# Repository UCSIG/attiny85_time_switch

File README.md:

# ATtiny85 Time Switch

## Low-power 12/24V time switch with undervoltage protection using the internal oscillator of the ATtiny85

The aim of this project is to switch a load on and off in regular time intervals. The device itself consumes only very little sleep current (~19.6uA on average).  
The device also monitors the supply voltage and turns off the load if the supply drops lower than the defined threshold.

## Features

- Clock calibration algorithm with values stored in the internal eeprom
- Supply voltage monitoring
- Jumper configuration for feature selection (supply voltage monitoring + time switch/only supply voltage monitoring)
- Jumper configuration for undervoltage threshold selection (12/24V)
- Low current consumption (~19.6uA)

## Specifications

| Type                        | Value        |
| --------------------------- | ------------ |
| Average Current Consumption | 19.6uA       |
| Maximum Load Current        | 5.7A (cont.) |
| Supply Voltages             | 12/24V       |
| Switch Type                 | Low-Side     |

## Detailed Description

There are three jumpers which must be set to either select the 12V or the 24V configuration. This changes the on/off times as well as the undervoltage thresholds.  
Every time the jumper configuration is changed, a reset must be performed for the changes to take effect.  

Upon coming out of reset, the device reads its clock calibration values stored in the internal eeprom to provide accurate timings for the time switch.

The device wakes up periodically and immediately goes back to sleep. That way, very long deep sleep periods can be reached.  
The ATtiny85 runs off of the internal 128kHz low speed oscillator during deep sleep. The watchdog timer wakes up the device every 8.192s (the maximum watchdog timeout) and the ATtiny increments a counter variable.
If it surpasses a pre-defined threshold, the load switch changes state from on->off or the other way round.  

Every 15 minutes it also measures the supply voltage and compares it to a pre-defined threshold. If the supply is lower than that threshold, the load is switched off until the device is reset.  
The maximum load current is determined by the sizing of the n-fet Q1. With the n-fet PMV20XNER one can switch up to 5/7A. The load is switched with a low side switch.  

The internal 8MHz oscillator of the ATtiny85 is used as the primary clock source. However, the clock frequency can vary by up to ±15%. In order to get accurate on/off times from the time switch,
this internal oscillator must be calibrated. A detailed description of how to do that can be found [here](clock_calibrations/clock_calibrations.md).

## Mechanical

The pcb is designed to fit in the [EL111](https://ide.es/eng/products/junction-boxes-and-mechanisms/ip65-ip67-junction-boxes/ref_EL111) enclosure by IDE electric.
It is screwed into the case using four M4 screws. The case itself is rated IP65-67. Its dimensions are 113x113x68 mm (Height x Width x Depth).

## Project structure

The code resides in the folder `src` and `include`. PlatformIO is chosen as the build environment. The best way to program the ATtiny85 is to use PlatformIO and VS Code as the IDE.  
The pcb project can be found under `pcb_project/attiny85_time_switch`. The relevant code snippets for changing the timing values and the undervoltage thresholds are at the top of `main.cpp`.
The gerber files are in `pcb_project/attiny85_time_switch/fabrication_outputs/`.

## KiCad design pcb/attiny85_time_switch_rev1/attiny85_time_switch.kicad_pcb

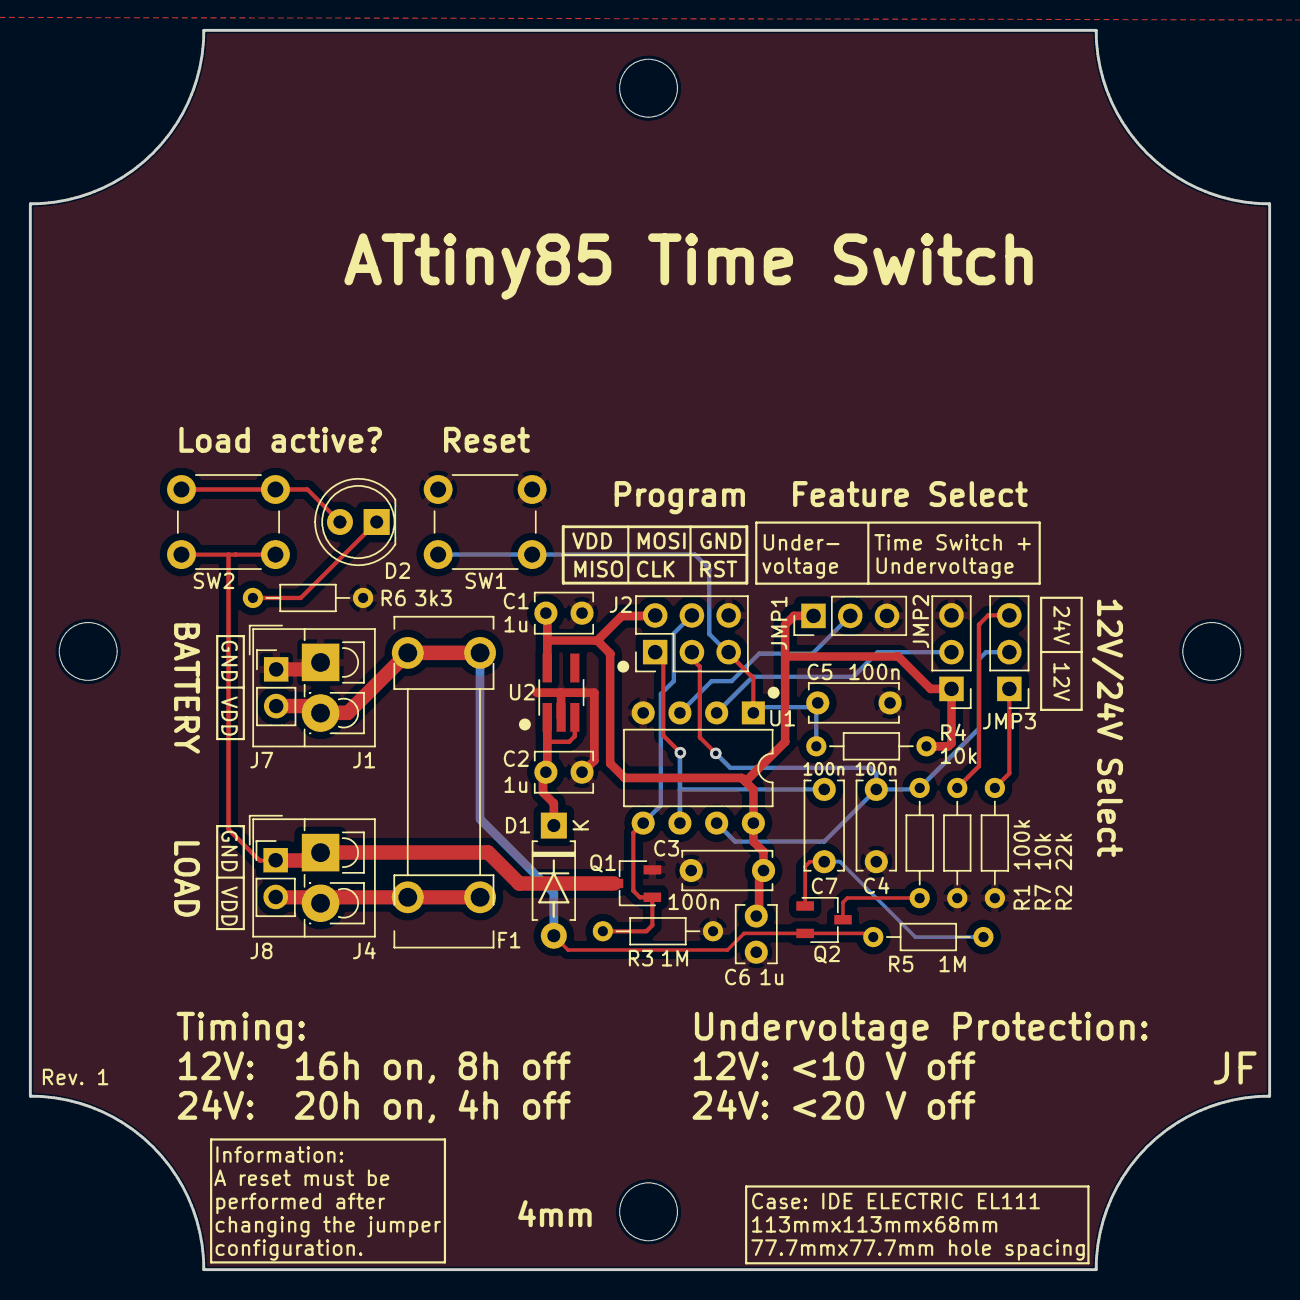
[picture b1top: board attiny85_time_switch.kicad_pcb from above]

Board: 2 copper layers, 85.7 x 85.7 mm, 32 parts (0 on the bottom side), 18 nets.

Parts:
C1, C2, C6: 1u; C_Disc_D3.8mm_W2.6mm_P2.50mm
C3, C4, C5, C7: 100n; C_Disc_D6.0mm_W2.5mm_P5.00mm
Case1: EL111; Case EL111
D1: D; D_A-405_P7.62mm_Horizontal
D2: LED; LED_D5.0mm
F1: 0751.0052; 0751.0052_Fuse
J1, J4: Screw_Terminal_01x02; TerminalBlock_4Ucon_1x02_P3.50mm_Vertical
J2: Conn_02x03_Odd_Even; PinHeader_2x03_P2.54mm_Vertical
J3, J5, J6: Conn_01x03_Pin; PinHeader_1x03_P2.54mm_Vertical
J7, J8: Conn_01x02_Pin; PinHeader_1x02_P2.54mm_Vertical
Q1: PMV20XNER; TSOT-23
Q2: BSS84AK; TSOT-23
R1: 100k; R_Axial_DIN0204_L3.6mm_D1.6mm_P7.62mm_Horizontal
R2: 22k; R_Axial_DIN0204_L3.6mm_D1.6mm_P7.62mm_Horizontal
R3, R5: 1M; R_Axial_DIN0204_L3.6mm_D1.6mm_P7.62mm_Horizontal
R4, R7: 10k; R_Axial_DIN0204_L3.6mm_D1.6mm_P7.62mm_Horizontal
R6: 3k3; R_Axial_DIN0204_L3.6mm_D1.6mm_P7.62mm_Horizontal
SW1: Reset; SW_PUSH_6mm_H5mm
SW2: Check FET; SW_PUSH_6mm_H5mm
U1: ATtiny85V-10P; DIP-8_W7.62mm
U2: AP7383-50W5-7; TSOT-23-5_HandSoldering

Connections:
12V_24V_SEL: J5.2, U1.2 (XTAL1/PB3)
ADC_BATTERY: C4.1, J2.3, J6.2, R1.2, U1.7 (PB2)
FEATURE_SELECT: J3.2, U1.3 (XTAL2/PB4)
GND: C1.2, C2.2, C3.2, C4.2, C5.2, C6.2, J1.1, J2.6, J3.3, J5.3, J7.1, Q1.2, R2.2, R3.2, R6.2, R7.2, SW1.1, U1.4 (GND), U2.2 (GND)
MISO: C7.2, J2.1, U1.6 (PB1)
MOSI: J2.4, Q1.1, R3.1, U1.5 (AREF/PB0)
unnamed: C7.1, Q2.1, R5.2
unnamed: C2.1, D1.1 (K), U2.1 (Vin), U2.3 (EN)
unnamed: D2.2 (A), SW2.2
unnamed: D2.1 (K), R6.1
unnamed: J4.1, J8.1, Q1.3, SW2.1
unnamed: F1.2, J4.2, J8.2
unnamed: J6.1, R2.1
unnamed: J6.3, R7.1
unnamed: Q2.3, R1.1
RESET: C5.1, J2.5, R4.2, SW1.2, U1.1 (~RESET/PB5)
VDD_MCU: C1.1, C3.1, C6.1, J2.2, J3.1, J5.1, R4.1, U1.8 (VCC), U2.5 (Vout)
VIN: D1.2 (A), F1.1, J1.2, J7.2, Q2.2, R5.1

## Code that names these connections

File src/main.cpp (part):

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/// E: 0xFF: Self-programming disabled.
///
/// Testing
/// L: 0x94: 128kHz. CKOUT: Clock out on PB4 feature select (no jumper!). Requires slow SCK programming clock (max 26kHz).
#include <Arduino.h>
#include <avr/sleep.h>
#include <avr/power.h>
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#include <EEPROM.h>

/// Define relevant pins.
#define VBAT_EN_PIN PB0
#define VDIV_EN_PIN PB1
#define ADC_BATTERY_PIN A1
#define SELECT_12_24V_PIN PB3
#define SELECT_FEATURE_PIN PB4

/// If defined, don't go to sleep but ensure the clock output can be measured on pin PB4 (feature select middle pin).
// #define CLOCK_CALIBRATION_MODE

/// 15min: Battery measurement period. The amount of wakeup cycles corresponding to 15min (8.192s per cycle). 15*60/8.192.
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
    // Read the ADC value (32*1023 = 32736 as a max value, fits in 16-bits).
    for (uint8_t adc_reading = 0u; adc_reading < ADC_AVERAGE_NUM; adc_reading++) {
        battery_voltage += analogRead(ADC_BATTERY_PIN);
    }

    // Divide the accumulated readings.
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
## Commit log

2023-08-07 🎉 Initial commit.
2023-08-07 📝 Updated readme.
2024-01-11 📝 Updated documentation on the zero power measurement link.
2024-02-07 Create LICENSE
2024-02-07 📝 Updated documentation.
2024-02-07 🚚 Renamed pcb project with revision.
2024-02-07 🧱 More renamin.
2025-08-16 📝 Update readme
